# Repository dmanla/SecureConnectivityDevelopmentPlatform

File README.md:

# Arduino-Mega Compatible Secure Connectivity Development Platform

**WARNING**: This project is under development and has not yet been validated.

This is an open hardware platform designed for the development of secure wired-network applications. It is fully compatible with all Arduino Mega-compatible hardware and software.

This project was inspired by (but not a copy of) the Freetronics EtherMega: https://github.com/freetronics/EtherMega
This project was created as an alternative to the platform offered by Freetronics.

Features:
- CH340 USB->Serial Converter (Functionally similar to FT232, Driver should be installed automatically)
- Jumper Configurable IO: Certain pins (D3, D6, D8, D9, D13) can be connected to the headers or to integrated peripheral pins.
- 5V 2A USB-C Input
- 6V - 32V VIN Input 
- MicroSD Card Slot
- 10/100 Ethernet provided over SPI using the W6100. Supports Auto-Negotiations, IPv4, IPv6, and Auto-MIDX.
- SE050 EdgeLock Plug and Trust Secure Element to provide security features for connected applications, accessible using I2C
- ISM330DHCX Inertial Measurement Unit, accessible using I2C
- MCP7940N Real Time Clock, accessible using I2C
- Level Shifted I2C: Provides connection points for 3V3 I2C Devices (Extra Header), and 5V I2C Devices (Standard Mega Headers)

## Top Render

## Bottom Render

## Side Render

## Relevant Datasheets

- [CH340N](https://datasheet.lcsc.com/szlcsc/Jiangsu-Qin-Heng-CH340C_C84681.pdf): USB->Serial Bridge
- [AP22805AW5](https://www.diodes.com/assets/Datasheets/AP22804_14.pdf): USB Protection
- [AP63205](https://www.diodes.com/assets/Datasheets/AP63200-AP63201-AP63203-AP63205.pdf): DC-DC Switching Converters
- [W6100](https://docs.wiznet.io/img/products/w6100/w6100_ds_v105e.pdf): SPI->Ethernet Bridge
- [ISM330DHCX](https://www.st.com/resource/en/datasheet/ism330dhcx.pdf): "AI Enabled" Inertial Measurement Unit
- [SE050C2HQ1](https://www.nxp.com/docs/en/data-sheet/SE050-DATASHEET.pdf): Security Coprocessor
- [MCP7940N](http://ww1.microchip.com/downloads/en/DeviceDoc/20005010F.pdf): Real-Time Clock **with** Battery Backup
- [Atmega2560](http://ww1.microchip.com/downloads/en/DeviceDoc/Atmel-2549-8-bit-AVR-Microcontroller-ATmega640-1280-1281-2560-2561_datasheet.pdf): Main Microcontroller

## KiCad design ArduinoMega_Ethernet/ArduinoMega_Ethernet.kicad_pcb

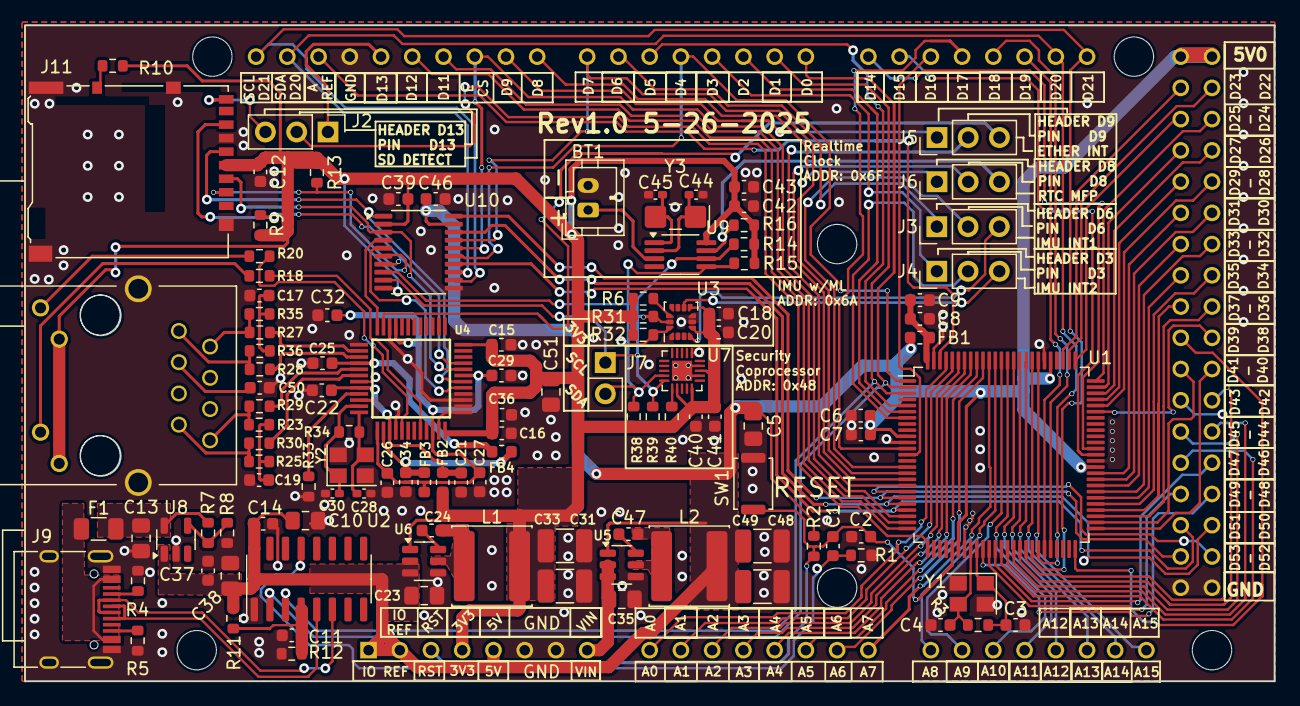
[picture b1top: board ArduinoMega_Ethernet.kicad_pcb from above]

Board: 2 copper layers, 101.6 x 53.3 mm, 116 parts (0 on the bottom side), 138 nets.

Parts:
A1: A000067; ARDUINO_A000067
BT1: Battery_Cell; JST_PH_B2B-PH-K_1x02_P2.00mm_Vertical
C1, C7, C8, C9, C11, C12, C14, C15, C16, C17, C18, C19, C21, C22, C24, C25, C26, C27, C29, C32, C37, C40, C42, C47, C50: 100nF; C_0603_1608Metric
C2, C3, C4: 22pF; C_0603_1608Metric
C5, C13, C23, C35, C38, C51: 10uF; C_0805_2012Metric_Pad1.18x1.45mm_HandSolder
C6, C20, C34, C36, C39, C41, C43, C46: 1uF; C_0603_1608Metric
C10: 4.7uF; C_0805_2012Metric_Pad1.18x1.45mm_HandSolder
C28, C30: 18pF; C_0402_1005Metric_Pad0.74x0.62mm_HandSolder
C31, C33, C48, C49: 22uF; C_1210_3225Metric_Pad1.33x2.70mm_HandSolder
C44, C45: 12pF; C_0402_1005Metric_Pad0.74x0.62mm_HandSolder
F1: Fuse; Fuse_1206_3216Metric
FB1, FB2, FB3, FB4: FerriteBead_Small; L_0603_1608Metric
J1: RB1-125BAG1A; WIZNET_RB1-125BAG1A
J2: SD_DET_JUMP; PinHeader_1x03_P2.54mm_Vertical
J3: IMU_INT1_JUMP; PinHeader_1x03_P2.54mm_Vertical
J4: IMU_INT2_JUMP; PinHeader_1x03_P2.54mm_Vertical
J5: ETHER_INT_JUMP; PinHeader_1x03_P2.54mm_Vertical
J6: RTC_MFP_JUMP; PinHeader_1x03_P2.54mm_Vertical
J7: EXT_3V3_I2C; PinHeader_1x02_P2.54mm_Vertical
J9: PROGRAM_POWER_USBC; USB_C_Receptacle_HRO_TYPE-C-31-M-12
J11: Micro_SD_Card_Det_Hirose_DM3AT; microSD_HC_Hirose_DM3AT-SF-PEJM5
L1: 3.9uH; L_APV_ANR6028
L2: 4.7uH; L_APV_ANR6028
R1, R2, R6, R9, R10, R13: 10k; R_0603_1608Metric
R3, R34: 1M; R_0603_1608Metric
R4, R5, R7: 5.1k; R_0603_1608Metric
R8: DNP; R_0603_1608Metric
R11: 22.1k; R_0603_1608Metric
R12: 47.5k; R_0603_1608Metric
R14, R15, R16, R31, R32, R38, R39, R40: 4.7k; R_0603_1608Metric
R18, R20: 470R; R_0603_1608Metric
R23, R25, R35, R36: 49.9R; R_0603_1608Metric
R27, R28, R29, R30: 3.3R; R_0603_1608Metric
R33: 12.3k; R_0603_1608Metric
SW1: SW_Push; SW_Push_SPST_NO_Alps_SKRK
U1: ATmega2560-16A; TQFP-100_14x14mm_P0.5mm
U2: CH340C; SOIC-16_3.9x9.9mm_P1.27mm
U3: ISM330DHCX; LGA-14_3x2.5mm_P0.5mm_LayoutBorder3x4y
U4: W6100L; QFP50P900X900X160-48N
U5: AP63205WU; TSOT-23-6
U6: AP63203WU; TSOT-23-6
U7: SE050C2HQ1; QFN-20-1EP_3x3mm_P0.4mm_EP1.65x1.65mm
U8: AP22804AW5; SOT-23-5
U9: MCP7940N-xST; MSOP-8_3x3mm_P0.65mm
U10: TXS0108EPW; TSSOP-20_4.4x6.5mm_P0.65mm
Y1: 16Mhz; Crystal_SMD_3225-4Pin_3.2x2.5mm
Y2: 25Mhz; Crystal_SMD_3225-4Pin_3.2x2.5mm
Y3: 32.768kHz; Crystal_SMD_EuroQuartz_EQ161-2Pin_3.2x1.5mm_HandSoldering

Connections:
+3.3VA: C50.1, J1.R3 (CT)
+3V3: A1.3V3 (+3V3), C12.2, C15.1, C16.1, C18.2, C20.2, C31.1, C33.1, C36.1, C39.2, C40.1, C41.1, C42.1, C43.1, C51.1, FB2.2, J1.L1, J1.L3, J11.4 (VDD), L1.2, R6.1, R9.1, R10.1, R13.1, R14.1, R15.1, R16.1, R31.1, R32.1, R38.1, R39.1, R40.1, U3.5 (VDD_IO), U3.8 (VDD), U4.24 (3V3D_1), U4.36 (3V3D_2), U6.1 (FB), U7.12 (VIN), U7.15 (VOUT), U7.18 (VCC), U9.8 (VCC), U10.2 (VCCA), U10.10 (OE)
+5V: A1.5V_1 (+5V_1), A1.5V_2 (+5V_2), A1.5V_3 (+5V_3), A1.IOREF, A1.NC, C5.2, C6.1, C7.1, C10.2, C14.2, C23.1, C37.2, C38.2, C46.2, C48.1, C49.1, FB1.1, L2.2, R2.1, R11.2, U1.10 (VCC), U1.31 (VCC), U1.61 (VCC), U1.80 (VCC), U2.16 (VCC), U5.1 (FB), U6.2 (EN), U6.3 (IN), U8.1 (OUT), U10.19 (VCCB)
/ETHER_CS: A1.10, U1.23 (PB4), U10.16 (B4)
/ETHER_~INT: J5.3, U4.47 (INTN)
/ETHER_~RST: A1.7, U1.16 (PH4), U10.17 (B3)
/HEAD_D3: A1.3, J4.1
/HEAD_D6: A1.6, J3.1
/HEAD_D8: A1.8, J6.1
/HEAD_D9: A1.9, J5.1
/HEAD_D13: A1.13, J2.1
/IMU_INT1: J3.3, U3.4 (INT1)
/IMU_INT2: J4.3, U3.9 (INT2)
/MCU_AREF_IN: A1.AREF, U1.98 (AREF)
/MCU_RESET: A1.RESET, C1.2, C2.2, R2.2, SW1.2, U1.30 (~RESET)
/PIN_A0: A1.AD0, U1.97 (PF0)
/PIN_A1: A1.AD1, U1.96 (PF1)
/PIN_A2: A1.AD2, U1.95 (PF2)
/PIN_A3: A1.AD3, U1.94 (PF3)
/PIN_A4: A1.AD4, U1.93 (PF4)
/PIN_A5: A1.AD5, U1.92 (PF5)
/PIN_A6: A1.AD6, U1.91 (PF6)
/PIN_A7: A1.AD7, U1.90 (PF7)
/PIN_A8: A1.AD8, U1.89 (PK0)
/PIN_A9: A1.AD9, U1.88 (PK1)
/PIN_A10: A1.AD10, U1.87 (PK2)
/PIN_A11: A1.AD11, U1.86 (PK3)
/PIN_A12: A1.AD12, U1.85 (PK4)
/PIN_A13: A1.AD13, U1.84 (PK5)
/PIN_A14: A1.AD14, U1.83 (PK6)
/PIN_A15: A1.AD15, U1.82 (PK7)
/PIN_D0: A1.0, U1.2 (PE0), U2.2 (TXD)
/PIN_D1: A1.1, U1.3 (PE1), U2.3 (RXD)
/PIN_D2: A1.2, U1.6 (PE4)
/PIN_D3: J4.2, U1.7 (PE5)
/PIN_D4/CS2: A1.4, U1.1 (PG5), U10.15 (B5)
/PIN_D5: A1.5, U1.5 (PE3)
/PIN_D6: J3.2, U1.15 (PH3)
/PIN_D8: J6.2, U1.17 (PH5)
/PIN_D9: J5.2, U1.18 (PH6)
/PIN_D11: A1.11, U1.24 (PB5)
/PIN_D12: A1.12, U1.25 (PB6)
/PIN_D13: J2.2, U1.26 (PB7)
/PIN_D14: A1.14, U1.64 (PJ1)
/PIN_D15: A1.15, U1.63 (PJ0)
/PIN_D16: A1.16, U1.13 (PH1)
/PIN_D17: A1.17, U1.12 (PH0)
/PIN_D18: A1.18, U1.46 (PD3)
/PIN_D19: A1.19, U1.45 (PD2)
/PIN_D20: A1.20, A1.SDA, U1.44 (PD1), U10.13 (B7)
/PIN_D21: A1.21, A1.SCL, U1.43 (PD0), U10.12 (B8)
/PIN_D22: A1.22, U1.78 (PA0)
/PIN_D23: A1.23, U1.77 (PA1)
/PIN_D24: A1.24, U1.76 (PA2)
/PIN_D25: A1.25, U1.75 (PA3)
/PIN_D26: A1.26, U1.74 (PA4)
/PIN_D27: A1.27, U1.73 (PA5)
/PIN_D28: A1.28, U1.72 (PA6)
/PIN_D29: A1.29, U1.71 (PA7)
/PIN_D30: A1.30, U1.60 (PC7)
/PIN_D31: A1.31, U1.59 (PC6)
/PIN_D32: A1.32, U1.58 (PC5)
/PIN_D33: A1.33, U1.57 (PC4)
/PIN_D34: A1.34, U1.56 (PC3)
/PIN_D35: A1.35, U1.55 (PC2)
/PIN_D36: A1.36, U1.54 (PC1)
/PIN_D37: A1.37, U1.53 (PC0)
/PIN_D38: A1.38, U1.50 (PD7)
/PIN_D39: A1.39, U1.70 (PG2)
/PIN_D40: A1.40, U1.52 (PG1)
/PIN_D41: A1.41, U1.51 (PG0)
/PIN_D42: A1.42, U1.42 (PL7)
/PIN_D43: A1.43, U1.41 (PL6)
/PIN_D44: A1.44, U1.40 (PL5)
/PIN_D45: A1.45, U1.39 (PL4)
/PIN_D46: A1.46, U1.38 (PL3)
/PIN_D47: A1.47, U1.37 (PL2)
/PIN_D48: A1.48, U1.36 (PL1)
/PIN_D49: A1.49, U1.35 (PL0)
/PIN_D50: A1.50, U1.22 (PB3), U10.14 (B6)
/PIN_D51: A1.51, U1.21 (PB2), U10.18 (B2)
/PIN_D52: A1.52, U1.20 (PB1), U10.20 (B1)
/PIN_D53: A1.53, U1.19 (PB0)
/PWRandPRG/1V2_ANA: C25.1, FB4.1, U4.4 (1V2A)
/PWRandPRG/1V2_DIG: C26.1, C27.1, C29.1, C32.1, FB3.1, U4.13 (1V2D_1), U4.22 (1V2D_2), U4.31 (1V2D_3), U4.45 (1V2D_4)
/PWRandPRG/1V2_OUT: C34.1, FB3.2, FB4.2, U4.14 (1V2O)
/PWRandPRG/3V3_ANA: C21.1, C22.1, FB2.1, U4.8 (3V3A_1), U4.15 (3V3A_2)
/PWRandPRG/ACT_LED: R18.1, U4.20 (ACTN)
/PWRandPRG/ETHERNET_CS: U4.29 (CSN), U10.5 (A4)
/PWRandPRG/ETHERNET_MISO: J11.7 (DAT0), R9.2, U4.33 (MISO), U10.7 (A6)
/PWRandPRG/ETHERNET_MOSI: J11.3 (CMD), U4.32 (MOSI), U10.3 (A2)
/PWRandPRG/ETHERNET_SCLK: J11.5 (CLK), U4.30 (SCLK), U10.1 (A1)
/PWRandPRG/ETHERNET_~RST: U4.48 (RSTN), U10.4 (A3)
/PWRandPRG/IMU_SCL: J7.1, R14.2, R31.2, R39.2, U3.13 (SCL), U7.10 (SCL), U9.6 (SCL), U10.9 (A8)
/PWRandPRG/IMU_SDA: J7.2, R15.2, R32.2, R38.2, U3.14 (SDA), U7.9 (SDA), U9.5 (SDA), U10.8 (A7)
/PWRandPRG/LINK_LED: R20.1, U4.17 (LNKN)
/PWRandPRG/PROGRAM_~DTR: C1.1, R1.1, U2.13 (~DTR)
/PWRandPRG/SDCARD_CS: J11.2 (DAT3/CD), R13.2, U10.6 (A5)
/PWRandPRG/SECURITY_ENA: R40.2, U7.11 (ENA)
/PWRandPRG/USBC_CC1: J9.A5 (CC1), R4.2
/PWRandPRG/USBC_CC2: J9.B5 (CC2), R5.2
/PWRandPRG/USBC_D+: J9.A6 (D+), J9.B6 (D+), U2.5 (UD+)
/PWRandPRG/USBC_D-: J9.A7 (D-), J9.B7 (D-), U2.6 (UD-)
/PWRandPRG/USBC_VBUS: C13.2, F1.1, R7.1, U8.5 (IN)
/RTC_MFP: J6.3, R16.2, U9.7 (MFP)
/SD_DET: J2.3, J11.9 (DET_B)
GND: A1.GND1, A1.GND2, A1.GND3, A1.GND4, A1.GND5, BT1.2 (-), C2.1, C3.1, C4.1, C5.1, C6.2, C7.2, C8.2, C9.2, C10.1, C11.1, C12.1, C13.1, C14.1, C15.2, C16.2, C17.2, C18.1, C19.2, C20.1, C21.2, C22.2, C23.2, C25.2, C26.2, C27.2, C28.1, C29.2, C30.1, C31.2, C32.2, C33.2, C34.2, C35.2, C36.2, C37.1, C38.1, C39.1, C40.2, C41.2, C42.2, C43.2, C44.1, C45.1, C46.1, C48.2, C49.2, C50.2, C51.2, J1.S1 (Shield), J1.S2 (Shield), J9.A1 (GND), J9.A12 (GND), J9.B1 (GND), J9.B12 (GND), J9.S1 (SHIELD), J11.6 (VSS), J11.11 (SHIELD), R1.2, R4.1, R5.1, R8.2, R12.1, R33.2, SW1.1, U1.11 (GND), U1.32 (GND), U1.62 (GND), U1.81 (GND), U1.99 (GND), U2.1 (GND), U3.1 (SDO/SA0), U3.6 (GND), U3.7 (GND), U4.1 (GNDA_1), U4.7 (GNDA_2), U4.10 (GND_1), U4.16 (GNDA_3), U4.23 (GND_2), U4.25 (MOD0), U4.26 (MOD1), U4.27 (MOD2), U4.28 (MOD3), U4.46 (GND_3), U5.4 (GND), U6.4 (GND), U7.1 (ISO14443), U7.17 (ISO14443_LA), U7.19 (VSS), U7.21 (EPAD), U8.2 (GND), U9.4 (VSS), U10.11 (GND), Y1.2, Y1.4, Y2.2, Y2.4
unnamed: BT1.1 (+), U9.3 (VBAT)
unnamed: C17.1, R35.2, R36.2
unnamed: C19.1, R23.2, R25.2
unnamed: F1.2, J9.A4 (VBUS), J9.A9 (VBUS), J9.B4 (VBUS), J9.B9 (VBUS)
unnamed: R33.1, U4.9 (RSET_BG)
unnamed: R29.1, U4.5 (RXIN)
unnamed: R30.1, U4.6 (RXIP)
unnamed: R27.1, U4.2 (TXON)
unnamed: R28.1, U4.3 (TXOP)
unnamed: C28.2, R34.2, U4.12 (XSCI), Y2.3
unnamed: C30.2, R34.1, U4.11 (XSCO), Y2.1
unnamed: J1.L2, R18.2
unnamed: J1.L4, R20.2
unnamed: J1.R7 (RD+), R25.1, R30.2
unnamed: J1.R8 (RD-), R23.1, R29.2
unnamed: J1.R1 (TD+), R28.2, R36.1
unnamed: J1.R2 (TD-), R27.2, R35.1
unnamed: J11.10 (DET_A), R10.2
unnamed: C8.1, C9.1, FB1.2, U1.100 (AVCC)
unnamed: C3.2, R3.1, U1.34 (XTAL1), Y1.1
unnamed: C4.2, R3.2, U1.33 (XTAL2), Y1.3
unnamed: C11.2, R11.1, R12.2, U2.4 (V3)
unnamed: R6.2, U3.12 (CS)
unnamed: C47.2, U5.6 (BST)
unnamed: C47.1, L2.1, U5.5 (SW)
unnamed: C24.2, U6.6 (BST)
unnamed: C24.1, L1.1, U6.5 (SW)
unnamed: R7.2, R8.1, U8.4 (EN)
unnamed: C45.2, U9.1 (X1), Y3.2
unnamed: C44.2, U9.2 (X2), Y3.1
VIN+: A1.VIN, C35.1, U5.2 (EN), U5.3 (IN)

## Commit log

2025-05-26 dual stack IP
2025-05-26 w6100 notes
2025-05-26 w6100 manufacturing and project files
2025-05-27 bom and component sizing
2025-05-27 w6100 datasheet
